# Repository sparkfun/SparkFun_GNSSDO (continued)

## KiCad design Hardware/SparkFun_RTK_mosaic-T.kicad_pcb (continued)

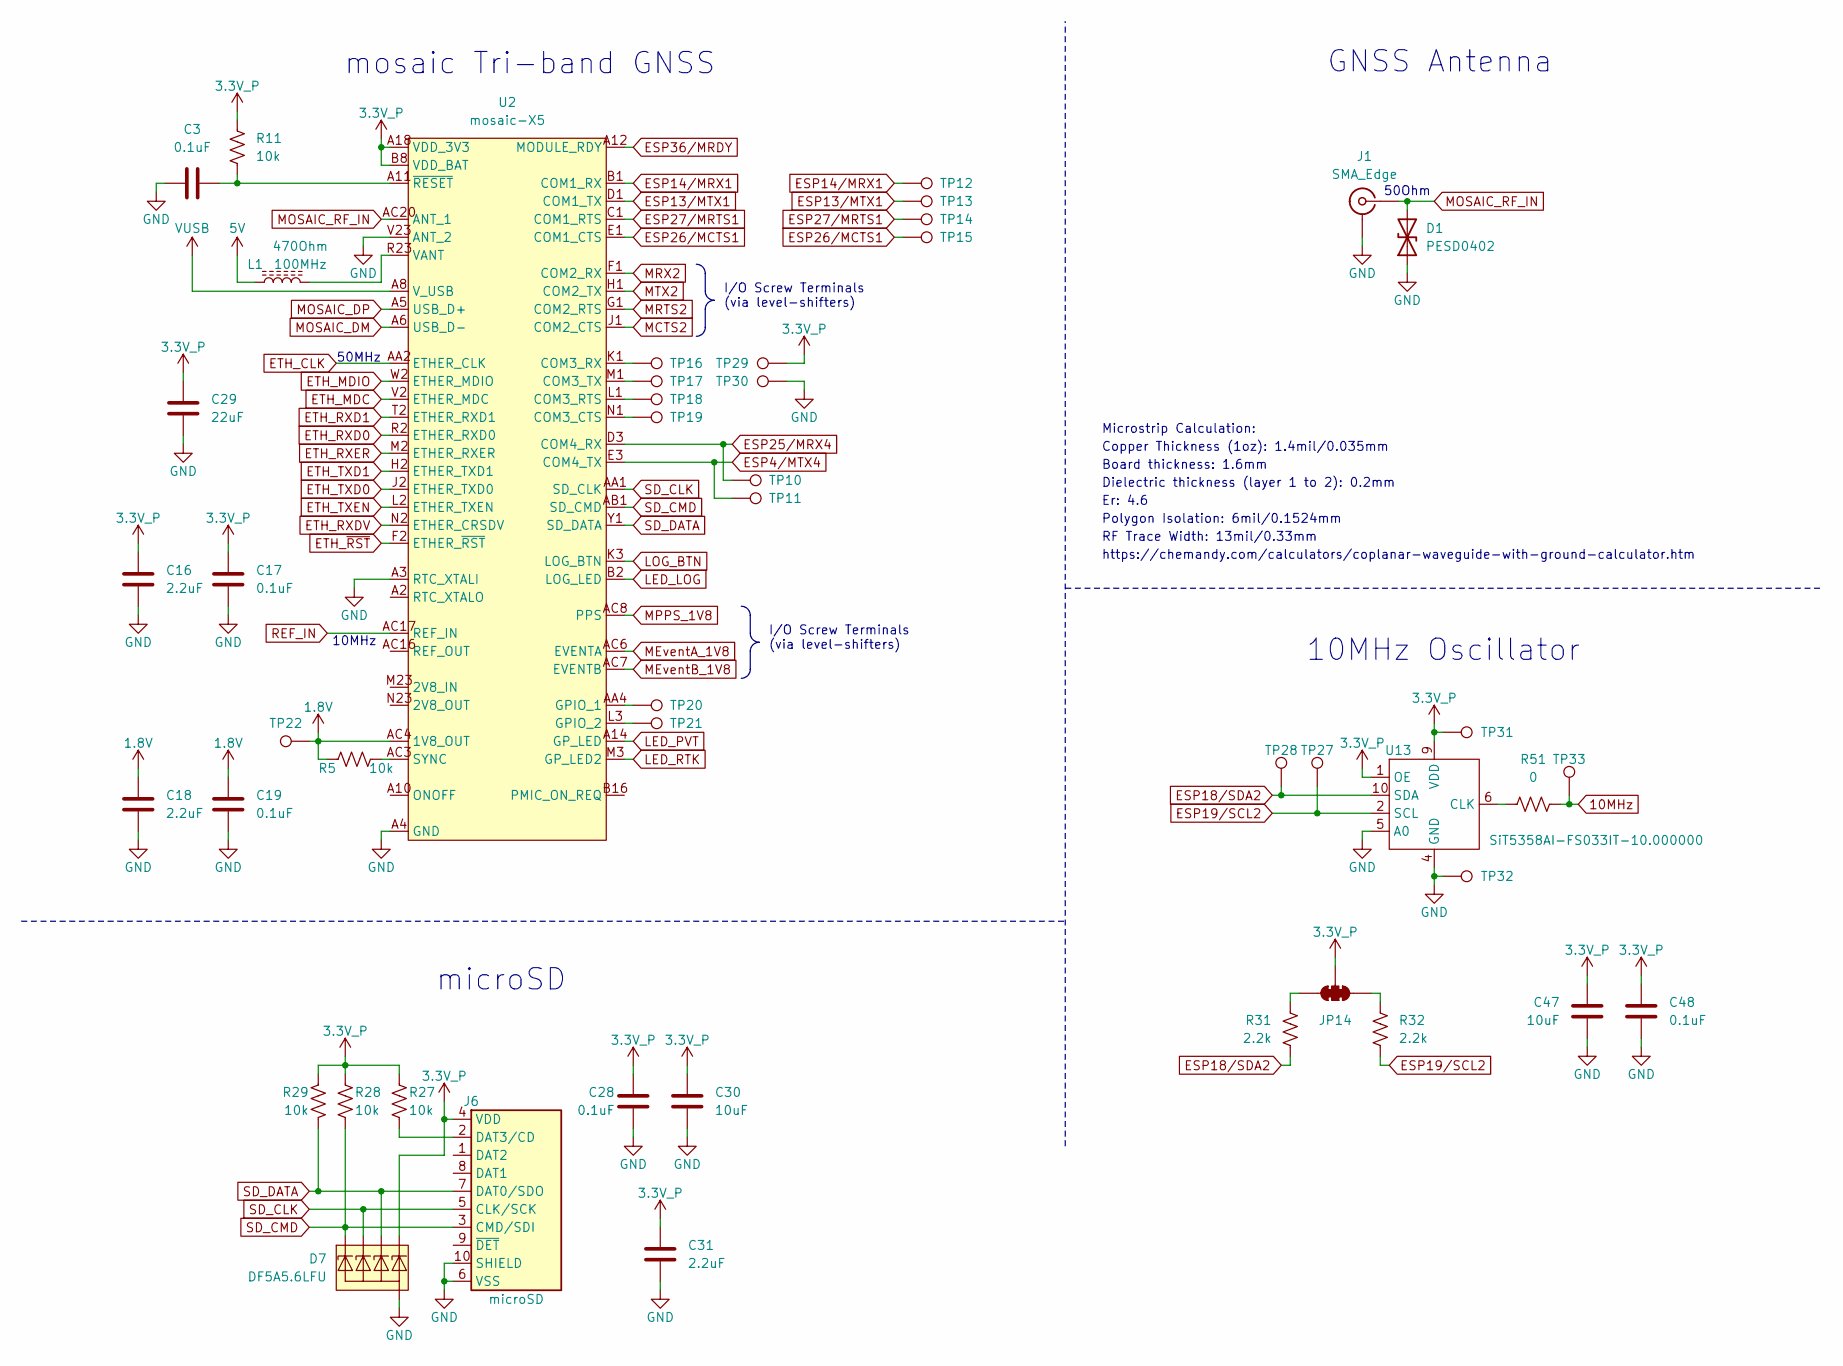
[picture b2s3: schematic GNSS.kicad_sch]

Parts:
C3, C17, C19, C28, C48: 0.1uF; C_0603_1608Metric; Voltage 25V; Tolerance 20%
C16, C18, C31: 2.2uF; C_0603_1608Metric; Voltage 10V; Tolerance 20%
C29: 22uF; C_0603_1608Metric; Voltage 6.3V; Tolerance 20%
C30, C47: 10uF; C_0603_1608Metric; Voltage 10V; Tolerance 20%
D1: PESD0402; C_0402_1005Metric
D7: DF5A5.6LFU; SOT-353
J1: SMA_Edge
J6: microSD; microSD_External_Pin
JP14: Jumper_3_NC-2_Trace
L1: 470Ohm; C_0603_1608Metric
R5, R11, R27, R28, R29: 10k; R_0603_1608Metric
R31, R32: 2.2k; R_0603_1608Metric
R51: 0; R_0603_1608Metric
TP10, TP11, TP12, TP13, TP14, TP15, TP16, TP17, TP18, TP19, TP20, TP21, TP22, TP27, TP28, TP29, TP30, TP31, TP32, TP33: PTH; 1x01
U2: mosaic-X5; MOSAIC_LGA
U13: SiT5358AI-FS033IT-10.000000; Ceramic_QFN_5.0x3.2mm-10

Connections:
1.8V: C18.1, C19.1, R5.2, TP22.1, U2.AC4 (1V8_OUT); also elsewhere on the board
3.3V_P: C16.1, C17.1, C28.1, C29.1, C30.1, C31.1, C47.1, C48.1, D7.5 (K4), J6.4 (VDD), JP14.2 (C), R11.2, R27.2, R28.2, R29.2, TP29.1, TP31.1, U2.A18 (VDD_3V3), U2.A19 (VDD_3V3), U2.A20 (VDD_3V3), U2.B8 (VDD_BAT), U2.B18 (VDD_3V3), U2.B19 (VDD_3V3), U2.B20 (VDD_3V3), U2.C18 (VDD_3V3), U2.C19 (VDD_3V3), U2.C20 (VDD_3V3), U13.1 (OE), U13.9 (VDD); also elsewhere on the board
5V: L1.1; also elsewhere on the board
10MHz: R51.1, TP33.1; also elsewhere on the board
ESP4/MTX4: TP11.1, U2.E3 (COM4_TX); also elsewhere on the board
ESP13/MTX1: TP13.1, U2.D1 (COM1_TX); also elsewhere on the board
ESP14/MRX1: TP12.1, U2.B1 (COM1_RX); also elsewhere on the board
ESP18/SDA2: R31.2, TP28.1, U13.10 (SDA); also elsewhere on the board
ESP19/SCL2: R32.2, TP27.1, U13.2 (SCL); also elsewhere on the board
ESP25/MRX4: TP10.1, U2.D3 (COM4_RX); also elsewhere on the board
ESP26/MCTS1: TP15.1, U2.E1 (COM1_CTS); also elsewhere on the board
ESP27/MRTS1: TP14.1, U2.C1 (COM1_RTS); also elsewhere on the board
ESP36/MRDY: U2.A12 (MODULE_RDY); also elsewhere on the board
ETH_CLK: U2.AA2 (ETHER_CLK); also elsewhere on the board
ETH_MDC: U2.V2 (ETHER_MDC); also elsewhere on the board
ETH_MDIO: U2.W2 (ETHER_MDIO); also elsewhere on the board
ETH_RXD0: U2.R2 (ETHER_RXD0); also elsewhere on the board
ETH_RXD1: U2.T2 (ETHER_RXD1); also elsewhere on the board
ETH_RXDV: U2.N2 (ETHER_CRSDV); also elsewhere on the board
ETH_RXER: U2.M2 (ETHER_RXER); also elsewhere on the board
ETH_TXD0: U2.J2 (ETHER_TXD0); also elsewhere on the board
ETH_TXD1: U2.H2 (ETHER_TXD1); also elsewhere on the board
ETH_TXEN: U2.L2 (ETHER_TXEN); also elsewhere on the board
ETH_~RST: U2.F2 (ETHER_~RST); also elsewhere on the board
GND: C3.1, C16.2, C17.2, C18.2, C19.2, C28.2, C29.2, C30.2, C31.2, C47.2, C48.2, D1.1 (A1), D7.2 (A), J1.2 (Ext), J6.6 (VSS), J6.10 (SHIELD), TP30.1, TP32.1, U2.A3 (RTC_XTALI), U2.A4 (GND), U2.A7 (GND), U2.A15 (GND), U2.A16 (GND), U2.A17 (GND), U2.A21 (GND), U2.A22 (GND), U2.A23 (GND), U2.AA13 (GND), U2.AA14 (GND), U2.AA15 (GND), U2.AA16 (GND), U2.AA17 (GND), U2.AA18 (GND), U2.AA19 (GND), U2.AA20 (GND), U2.AA21 (GND), U2.AA22 (GND), U2.AA23 (GND), U2.AB2 (GND), U2.AB3 (GND), U2.AB4 (GND), U2.AB5 (GND), U2.AB6 (GND), U2.AB7 (GND), U2.AB8 (GND), U2.AB13 (GND), U2.AB14 (GND), U2.AB15 (GND), U2.AB16 (GND), U2.AB17 (GND), U2.AB18 (GND), U2.AB19 (GND), U2.AB20 (GND), U2.AB21 (GND), U2.AB22 (GND), U2.AB23 (GND), U2.AC13 (GND), U2.AC15 (GND), U2.AC18 (GND), U2.AC19 (GND), U2.AC21 (GND), U2.AC22 (GND), U2.AC23 (GND), U2.B4 (GND), U2.B5 (GND), U2.B6 (GND), U2.B7 (GND), U2.B13 (GND), U2.B17 (GND), U2.B21 (GND), U2.C4 (GND), U2.C7 (GND), U2.C15 (GND), U2.C16 (GND), U2.C17 (GND), U2.C23 (GND), U2.D2 (GND), U2.D21 (GND), U2.D22 (GND), U2.D23 (GND), U2.E2 (GND), U2.E21 (GND), U2.E22 (GND), U2.E23 (GND), U2.F21 (GND), U2.F22 (GND), U2.F23 (GND), U2.G2 (GND), U2.G21 (GND), U2.G23 (GND), U2.H21 (GND), U2.H22 (GND), U2.H23 (GND), U2.J21 (GND), U2.J22 (GND), U2.J23 (GND), U2.K2 (GND), U2.K21 (GND), U2.K22 (GND), U2.K23 (GND), U2.L21 (GND), U2.L22 (GND), U2.L23 (GND), U2.M21 (GND), U2.M22 (GND), U2.N21 (GND), U2.N22 (GND), U2.P1 (GND), U2.P2 (GND), U2.P3 (GND), U2.P21 (GND), U2.P22 (GND), U2.R3 (GND), U2.R21 (GND), U2.R22 (GND), U2.T21 (GND), U2.T22 (GND), U2.T23 (GND), U2.U2 (GND), U2.U21 (GND), U2.U22 (GND), U2.U23 (GND), U2.V21 (GND), U2.V22 (GND), U2.V23 (ANT_2), U2.W21 (GND), U2.W22 (GND), U2.W23 (GND), U2.Y2 (GND), U2.Y21 (GND), U2.Y22 (GND), U2.Y23 (GND), U13.4 (GND), U13.5 (A0); also elsewhere on the board
LED_LOG: U2.B2 (LOG_LED); also elsewhere on the board
LED_PVT: U2.A14 (GP_LED); also elsewhere on the board
LED_RTK: U2.M3 (GP_LED2); also elsewhere on the board
LOG_BTN: U2.K3 (LOG_BTN); also elsewhere on the board
MCTS2: U2.J1 (COM2_CTS); also elsewhere on the board
MEventA_1V8: U2.AC6 (EVENTA); also elsewhere on the board
MEventB_1V8: U2.AC7 (EVENTB); also elsewhere on the board
MOSAIC_DM: U2.A6 (USB_D-); also elsewhere on the board
MOSAIC_DP: U2.A5 (USB_D+); also elsewhere on the board
MOSAIC_RF_IN: D1.2 (A2), J1.1 (In), U2.AC20 (ANT_1)
MPPS_1V8: U2.AC8 (PPS); also elsewhere on the board
MRTS2: U2.G1 (COM2_RTS); also elsewhere on the board
MRX2: U2.F1 (COM2_RX); also elsewhere on the board
MTX2: U2.H1 (COM2_TX); also elsewhere on the board
unnamed: J6.2 (DAT3/CD), R27.1
unnamed: JP14.1 (A), R32.1
unnamed: JP14.3 (B), R31.1
unnamed: TP19.1, U2.N1 (COM3_CTS)
unnamed: TP18.1, U2.L1 (COM3_RTS)
unnamed: TP16.1, U2.K1 (COM3_RX)
unnamed: TP17.1, U2.M1 (COM3_TX)
unnamed: TP20.1, U2.AA4 (GPIO_1)
unnamed: TP21.1, U2.L3 (GPIO_2)
unnamed: R5.1, U2.AC3 (SYNC)
unnamed: C3.2, R11.1, U2.A11 (~RESET)
unnamed: R51.2, U13.6 (CLK)
REF_IN: U2.AC17 (REF_IN); also elsewhere on the board
SD_CLK: D7.3 (K2), J6.5 (CLK/SCK), U2.AA1 (SD_CLK)
SD_CMD: D7.1 (K1), J6.3 (CMD/SDI), R28.1, U2.AB1 (SD_CMD)
SD_DATA: D7.4 (K3), J6.7 (DAT0/SDO), R29.1, U2.Y1 (SD_DATA)
VANT: L1.2, U2.P23 (VANT), U2.R23 (VANT)
VUSB: U2.A8 (V_USB); also elsewhere on the board

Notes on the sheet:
Er: 4.6
Polygon Isolation: 6mil/0.1524mm
10MHz
I/O Screw Terminals (via level-shifters)
10MHz Oscillator
Dielectric thickness (layer 1 to 2): 0.2mm
Board thickness: 1.6mm
mosaic Tri-band GNSS
Microstrip Calculation:
50Ohm
https://chemandy.com/calculators/coplanar-waveguide-with-ground-calculator.htm
Copper Thickness (1oz): 1.4mil/0.035mm
50MHz
GNSS Antenna
microSD
RF Trace Width: 13mil/0.33mm

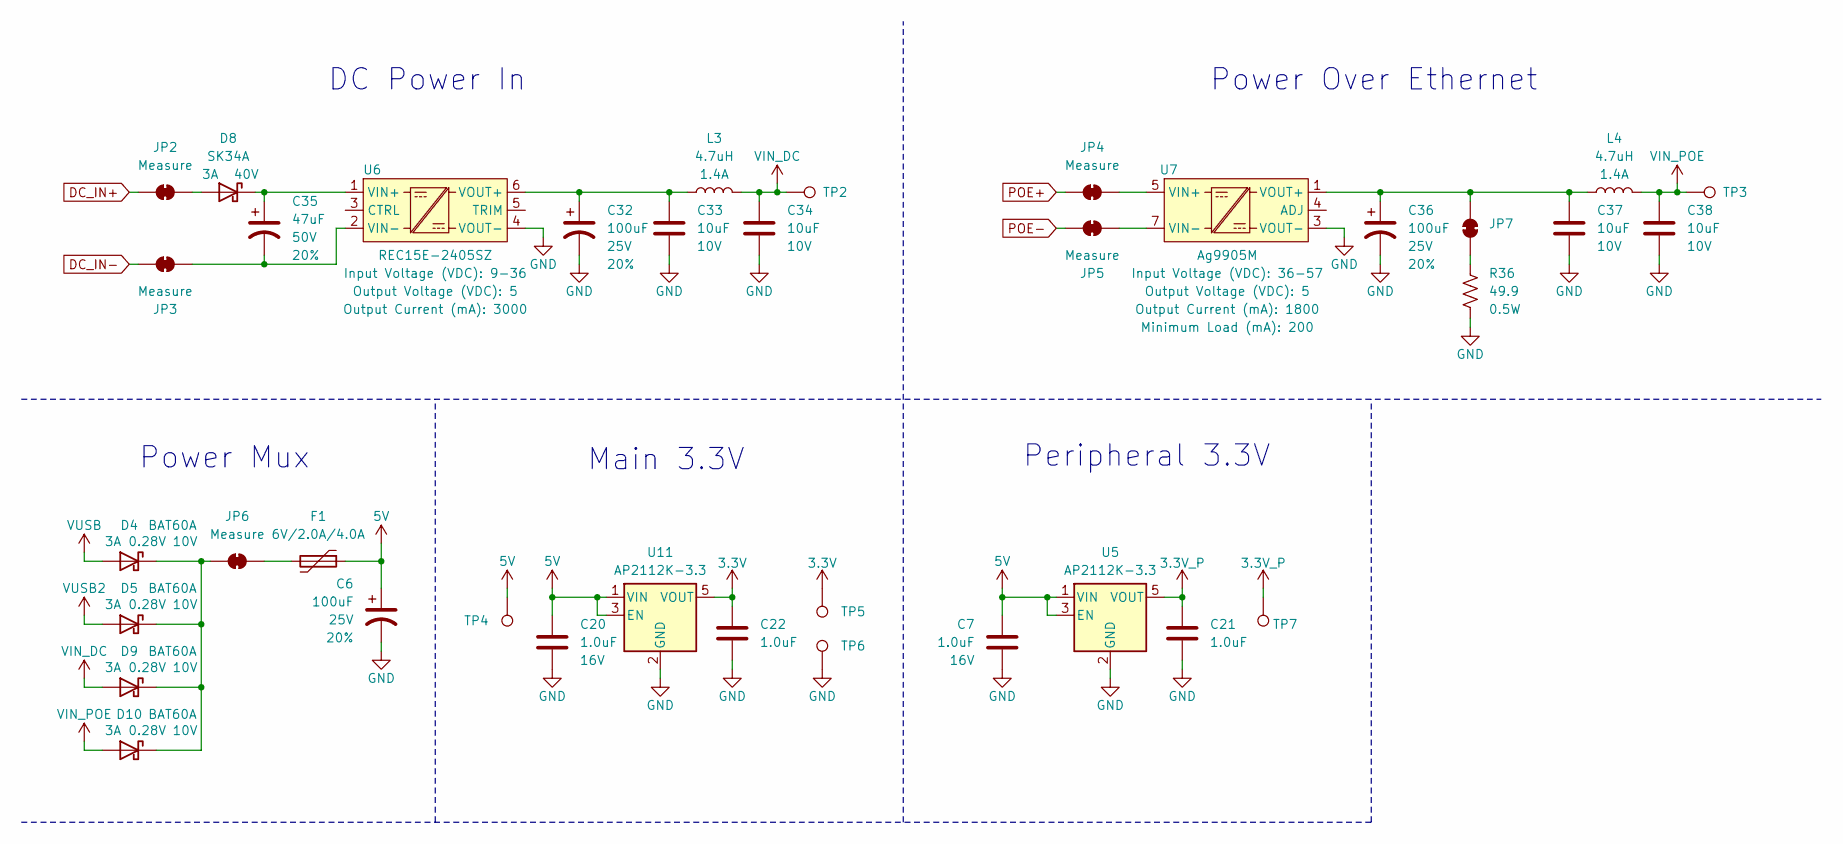
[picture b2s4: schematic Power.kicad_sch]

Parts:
C6, C32, C36: 100uF; PANASONIC_D; Voltage 25V; Tolerance 20%
C7, C20, C21, C22: 1.0uF; C_0603_1608Metric; Voltage 16V; Tolerance 10%
C33, C34, C37, C38: 10uF; C_0603_1608Metric; Voltage 10V; Tolerance 20%
C35: 47uF; PANASONIC_D; Voltage 50V; Tolerance 20%
D4, D5, D9, D10: BAT60A; SOD-323
D8: SK34A; SMA
F1: 6V/2.0A/4.0A; 1210
JP2, JP3, JP4, JP5, JP6: Measure; Jumper_2_PTH_SMD_Combo-NC
JP7: Jumper_2_NC_Trace
L3, L4: 4.7uH; 1008_2520Metric
R36: 49.9; R_1206_3216Metric; Tolerance 1%
TP2, TP3, TP4, TP5, TP6, TP7: PTH; 1x01
U5, U11: AP2112K-3.3; SOT23-5
U6: REC15E-2405SZ; REC15E; Input Voltage (VDC) 9-36; Output Voltage (VDC) 5
U7: Ag9905M; Ag9900M; Input Voltage (VDC) 36-57; Output Voltage (VDC) 5

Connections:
3.3V: C22.1, TP5.1, U11.5 (VOUT); also elsewhere on the board
3.3V_P: C21.1, TP7.1, U5.5 (VOUT); also elsewhere on the board
5V: C6.1, C7.1, C20.1, F1.1, TP4.1, U5.1 (VIN), U5.3 (EN), U11.1 (VIN), U11.3 (EN); also elsewhere on the board
DC_IN+: JP2.1 (A); also elsewhere on the board
DC_IN-: JP3.1 (A); also elsewhere on the board
GND: C6.2, C7.2, C20.2, C21.2, C22.2, C32.2, C33.2, C34.2, C36.2, C37.2, C38.2, R36.1, TP6.1, U5.2 (GND), U6.4 (VOUT-), U7.3 (VOUT-), U11.2 (GND); also elsewhere on the board
unnamed: D8.A, JP2.2 (B)
unnamed: C35.2, JP3.2 (B), U6.2 (VIN-)
unnamed: D4.C, D5.C, D9.C, D10.C, JP6.1 (A)
unnamed: F1.2, JP6.2 (B)
unnamed: JP7.1 (A), R36.2
unnamed: C36.1, C37.1, JP7.2 (B), L4.1, U7.1 (VOUT+), U7.2 (VOUT+)
unnamed: C35.1, D8.C, U6.1 (VIN+)
unnamed: C32.1, C33.1, L3.1, U6.6 (VOUT+)
POE+: JP4.1 (A); also elsewhere on the board
POE-: JP5.1 (A); also elsewhere on the board
VIN+: JP4.2 (B), U7.5 (VIN+), U7.6 (VIN+)
VIN-: JP5.2 (B), U7.7 (VIN-), U7.8 (VIN-)
VIN_DC: C34.1, D9.A, L3.2, TP2.1
VIN_POE: C38.1, D10.A, L4.2, TP3.1
VUSB: D4.A; also elsewhere on the board
VUSB2: D5.A; also elsewhere on the board

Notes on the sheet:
Power Over Ethernet
DC Power In
Peripheral 3.3V
Power Mux
Main 3.3V

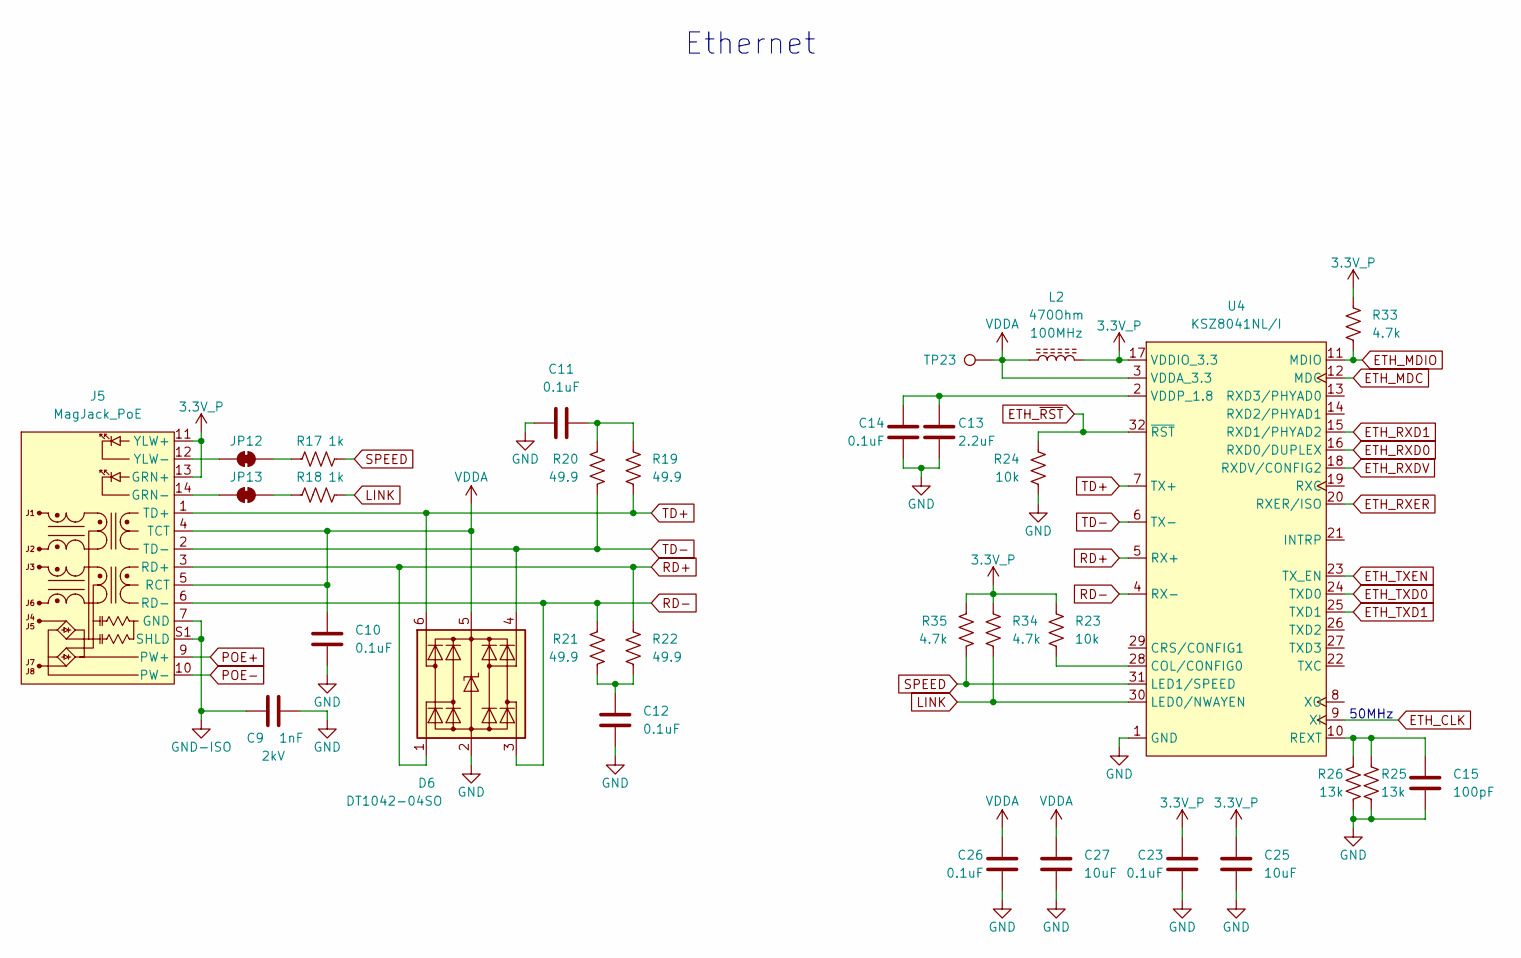
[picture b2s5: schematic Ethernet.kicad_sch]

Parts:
C9: 1nF; C_1206_3216Metric; Voltage 2kV; Tolerance 10%
C10, C11, C12, C14, C23, C26: 0.1uF; C_0603_1608Metric; Voltage 25V; Tolerance 20%
C13: 2.2uF; C_0603_1608Metric; Voltage 10V; Tolerance 20%
C15: 100pF; C_0603_1608Metric; Voltage 50V; Tolerance 10%
C25, C27: 10uF; C_0603_1608Metric; Voltage 10V; Tolerance 20%
D6: DT1042-04SO; SOT23-6
J5: MagJack_PoE; MagJack_PoE_RJ45
JP12, JP13: Jumper_2_NC_Trace
L2: 470Ohm; C_0603_1608Metric
R17, R18: 1k; R_0603_1608Metric
R19, R20, R21, R22: 49.9; R_0603_1608Metric; Tolerance 1%
R23, R24: 10k; R_0603_1608Metric
R25, R26: 13k; R_0603_1608Metric
R33, R34, R35: 4.7k; R_0603_1608Metric
TP23: PTH; 1x01
U4: KSZ8041NL/I; QFN-32

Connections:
3.3V_P: C23.1, C25.1, J5.11 (YLW+), J5.13 (GRN+), L2.2, R23.2, R33.1, R34.1, R35.1, U4.17 (VDDIO_3.3); also elsewhere on the board
ETH_CLK: U4.9 (XI); also elsewhere on the board
ETH_MDC: U4.12 (MDC); also elsewhere on the board
ETH_MDIO: R33.2, U4.11 (MDIO); also elsewhere on the board
ETH_RXD0: U4.16 (RXD0/DUPLEX); also elsewhere on the board
ETH_RXD1: U4.15 (RXD1/PHYAD2); also elsewhere on the board
ETH_RXDV: U4.18 (RXDV/CONFIG2); also elsewhere on the board
ETH_RXER: U4.20 (RXER/ISO); also elsewhere on the board
ETH_TXD0: U4.24 (TXD0); also elsewhere on the board
ETH_TXD1: U4.25 (TXD1); also elsewhere on the board
ETH_TXEN: U4.23 (TX_EN); also elsewhere on the board
ETH_~RST: R24.1, U4.32 (~RST); also elsewhere on the board
GND: C9.2, C10.2, C11.1, C12.2, C13.2, C14.2, C15.2, C23.2, C25.2, C26.2, C27.2, D6.2 (GND), R24.2, R25.2, R26.2, U4.1 (GND), U4.EP (GND); also elsewhere on the board
GND-ISO: C9.1, J5.7 (GND), J5.S1 (SHLD), J5.S2 (SHLD)
LINK: R18.1, R34.2, U4.30 (LED0/NWAYEN)
unnamed: C11.2, R19.1, R20.1
unnamed: C12.1, R21.2, R22.2
unnamed: J5.14 (GRN-), JP13.1 (A)
unnamed: J5.12 (YLW-), JP12.1 (A)
unnamed: JP12.2 (B), R17.2
unnamed: JP13.2 (B), R18.2
unnamed: R23.1, U4.28 (COL/CONFIG0)
unnamed: C15.1, R25.1, R26.1, U4.10 (REXT)
unnamed: C13.1, C14.1, U4.2 (VDDP_1.8)
POE+: J5.9 (PW+); also elsewhere on the board
POE-: J5.10 (PW-); also elsewhere on the board
RD+: D6.1 (I/O1), J5.3 (RD+), R22.1, U4.5 (RX+)
RD-: D6.3 (I/O2), J5.6 (RD-), R21.1, U4.4 (RX-)
SPEED: R17.1, R35.2, U4.31 (LED1/SPEED)
TD+: D6.6 (I/O4), J5.1 (TD+), R19.2, U4.7 (TX+)
TD-: D6.4 (I/O3), J5.2 (TD-), R20.2, U4.6 (TX-)
VDDA: C10.1, C26.1, C27.1, D6.5 (VCC), J5.4 (TCT), J5.5 (RCT), L2.1, TP23.1, U4.3 (VDDA_3.3)

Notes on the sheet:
50MHz
Ethernet

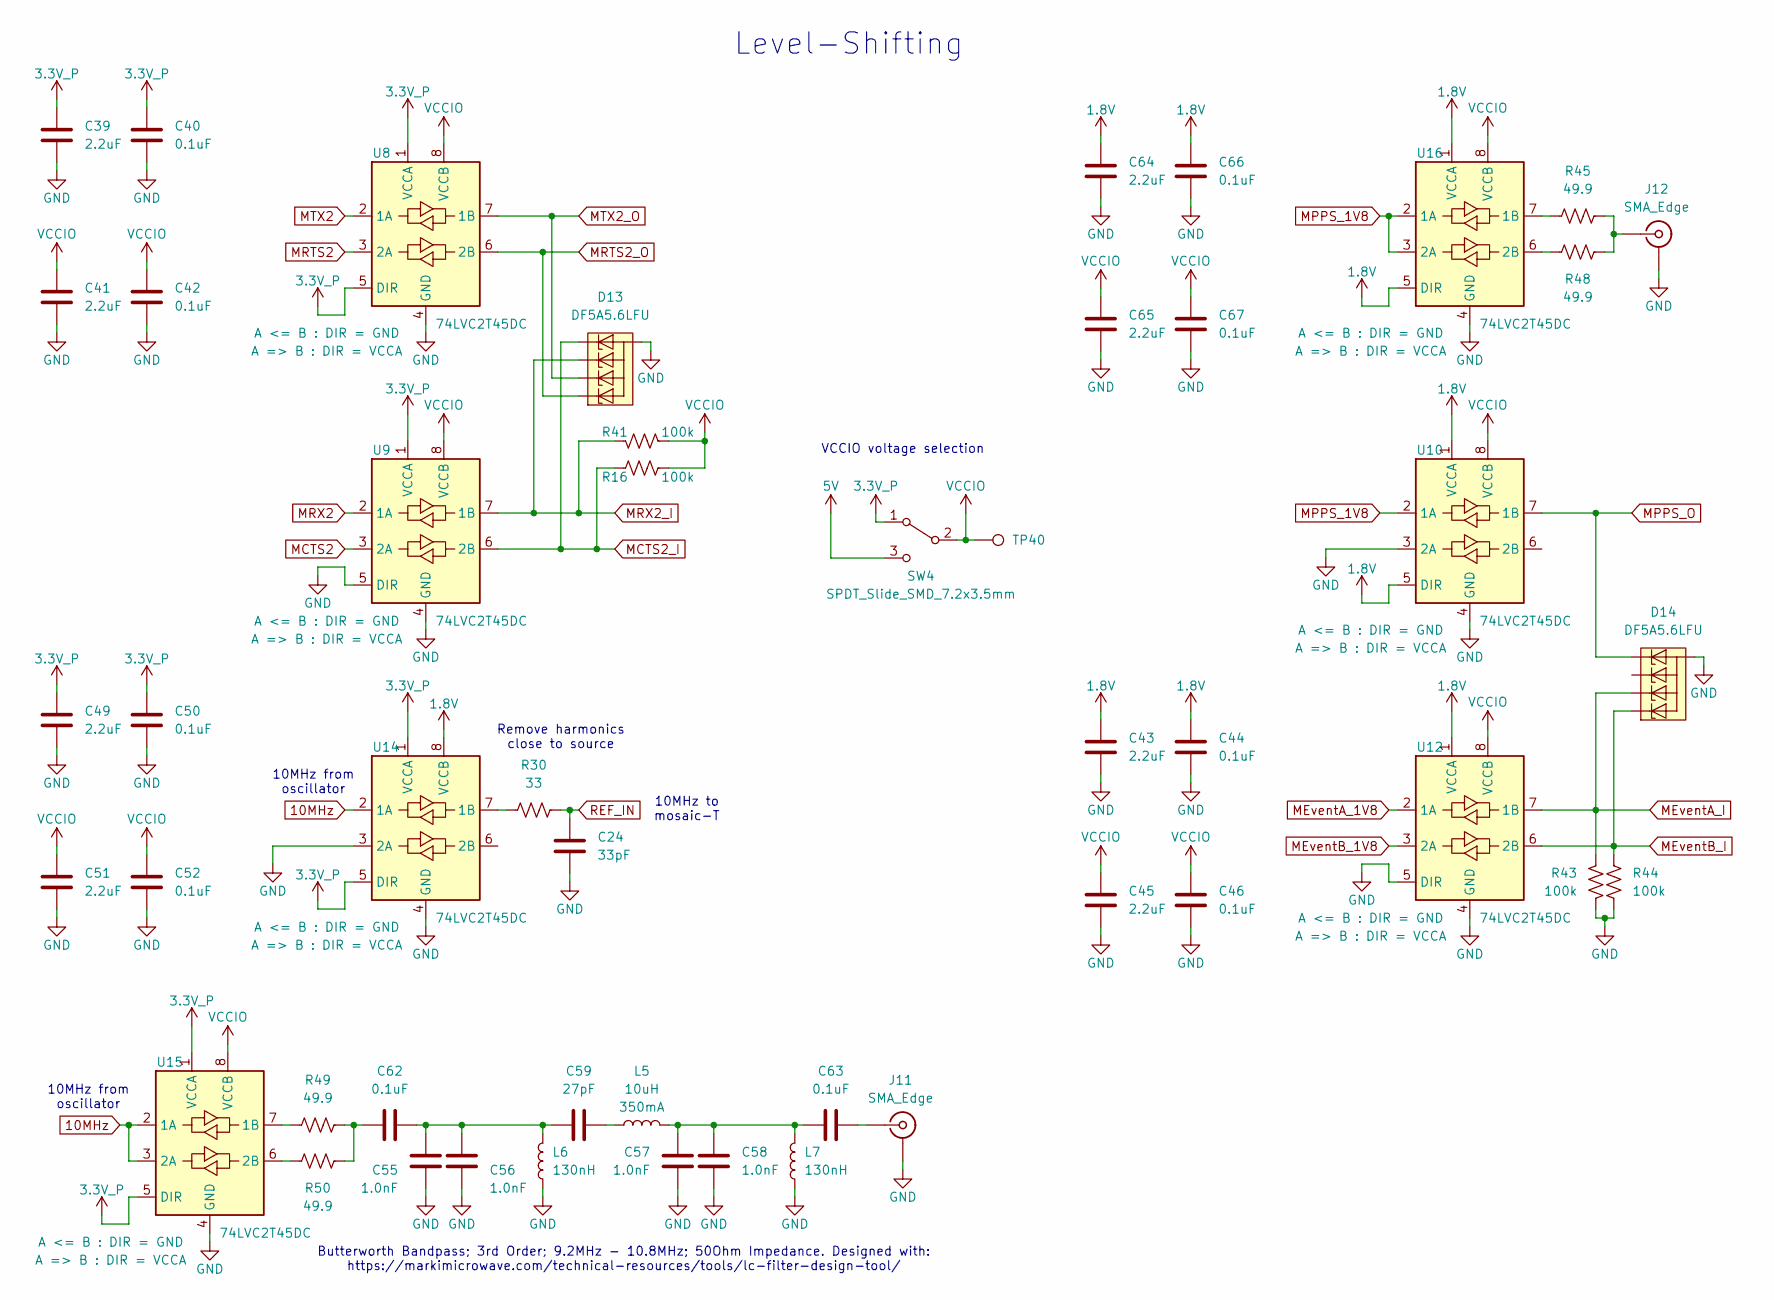
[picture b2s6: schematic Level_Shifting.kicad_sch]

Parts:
C24: 33pF; C_0603_1608Metric; Voltage 50V; Tolerance 5%
C39, C41, C43, C45, C49, C51, C64, C65: 2.2uF; C_0603_1608Metric; Voltage 10V; Tolerance 20%
C40, C42, C44, C46, C50, C52, C62, C63, C66, C67: 0.1uF; C_0603_1608Metric; Voltage 25V; Tolerance 20%
C55, C56, C57, C58: 1.0nF; C_0603_1608Metric; Voltage 50V; Tolerance 10%
C59: 27pF; C_0603_1608Metric; Voltage 50V; Tolerance 5%
D13, D14: DF5A5.6LFU; SOT-353
J11, J12: SMA_Edge
L5: 10uH; C_0805_2012Metric
L6, L7: 130nH; C_0603_1608Metric
R16, R41, R43, R44: 100k; R_0603_1608Metric
R30: 33; R_0603_1608Metric
R45, R48, R49, R50: 49.9; R_0603_1608Metric; Tolerance 1%
SW4: SPDT_Slide_SMD_7.2x3.5mm; Slide_DPDT_SMD_7.2x3.5mm; Mrg Part# AYZ0202
TP40: PTH; 1x01
U8, U9, U10, U12, U14, U15, U16: 74LVC2T45DC; VSSOP8_SOT765-1

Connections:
1.8V: C43.1, C44.1, C64.1, C66.1, U10.1 (VCCA), U10.5 (DIR), U12.1 (VCCA), U14.8 (VCCB), U16.1 (VCCA), U16.5 (DIR); also elsewhere on the board
3.3V_P: C39.1, C40.1, C49.1, C50.1, SW4.1 (A), U8.1 (VCCA), U8.5 (DIR), U9.1 (VCCA), U14.1 (VCCA), U14.5 (DIR), U15.1 (VCCA), U15.5 (DIR); also elsewhere on the board
5V: SW4.3 (C); also elsewhere on the board
10MHz: U14.2 (1A), U15.2 (1A), U15.3 (2A); also elsewhere on the board
GND: C24.2, C39.2, C40.2, C41.2, C42.2, C43.2, C44.2, C45.2, C46.2, C49.2, C50.2, C51.2, C52.2, C55.2, C56.2, C57.2, C58.2, C64.2, C65.2, C66.2, C67.2, D13.2 (A), D14.2 (A), J11.2 (Ext), J12.2 (Ext), L6.1, L7.1, R43.2, R44.2, U8.4 (GND), U9.4 (GND), U9.5 (DIR), U10.3 (2A), U10.4 (GND), U12.4 (GND), U12.5 (DIR), U14.3 (2A), U14.4 (GND), U15.4 (GND), U16.4 (GND); also elsewhere on the board
MCTS2: U9.3 (2A); also elsewhere on the board
MCTS2_I: D13.5 (K4), R16.2, U9.6 (2B); also elsewhere on the board
MEventA_1V8: U12.2 (1A); also elsewhere on the board
MEventA_I: D14.3 (K2), R43.1, U12.7 (1B); also elsewhere on the board
MEventB_1V8: U12.3 (2A); also elsewhere on the board
MEventB_I: D14.1 (K1), R44.1, U12.6 (2B); also elsewhere on the board
MPPS_1V8: U10.2 (1A), U16.2 (1A), U16.3 (2A); also elsewhere on the board
MPPS_O: D14.5 (K4), U10.7 (1B); also elsewhere on the board
MRTS2: U8.3 (2A); also elsewhere on the board
MRTS2_O: D13.1 (K1), U8.6 (2B); also elsewhere on the board
MRX2: U9.2 (1A); also elsewhere on the board
MRX2_I: D13.4 (K3), R41.2, U9.7 (1B); also elsewhere on the board
MTX2: U8.2 (1A); also elsewhere on the board
MTX2_O: D13.3 (K2), U8.7 (1B); also elsewhere on the board
unnamed: C55.1, C56.1, C59.1, C62.2, L6.2
unnamed: C57.1, C58.1, C63.1, L5.2, L7.2
unnamed: C59.2, L5.1
unnamed: C62.1, R49.1, R50.1
unnamed: C63.2, J11.1 (In)
unnamed: J12.1 (In), R45.1, R48.1
unnamed: R30.2, U14.7 (1B)
unnamed: R49.2, U15.7 (1B)
unnamed: R50.2, U15.6 (2B)
unnamed: R45.2, U16.7 (1B)
unnamed: R48.2, U16.6 (2B)
REF_IN: C24.1, R30.1; also elsewhere on the board
VCCIO: C41.1, C42.1, C45.1, C46.1, C51.1, C52.1, C65.1, C67.1, R16.1, R41.1, SW4.2 (B), TP40.1, U8.8 (VCCB), U9.8 (VCCB), U10.8 (VCCB), U12.8 (VCCB), U15.8 (VCCB), U16.8 (VCCB); also elsewhere on the board

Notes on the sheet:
10MHz from oscillator
Remove harmonics close to source
Level-Shifting
Butterworth Bandpass; 3rd Order; 9.2MHz - 10.8MHz; 50Ohm Impedance. Designed with: https://markimicrowave.com/technical-resources/tools/lc-filter-design-tool/
10MHz to mosaic-T
VCCIO voltage selection

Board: 4 copper layers, 339 parts (87 on the bottom side), 155 nets, no tracks yet.

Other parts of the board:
Ref**: Val**; OSHW_Logo_5mm
Ref**#2: Val**; SparkFun_RTK_15mm
kibuzzard-65A7F5A7: G***; kibuzzard-65A7F5A7
kibuzzard-65A7F5BC: G***; kibuzzard-65A7F5BC
kibuzzard-65A7F5CF: G***; kibuzzard-65A7F5CF
kibuzzard-65A7F5E3: G***; kibuzzard-65A7F5E3
kibuzzard-65A7F440, kibuzzard-65A7F440#2: G***; kibuzzard-65A7F440
kibuzzard-65A7F499: G***; kibuzzard-65A7F499
kibuzzard-65A7F511, kibuzzard-65A7F511#2: G***; kibuzzard-65A7F511
kibuzzard-65A7F548, kibuzzard-65A7F548#2: G***; kibuzzard-65A7F548
kibuzzard-65A7F771, kibuzzard-65A7F771#2: G***; kibuzzard-65A7F771
kibuzzard-65A7F891, kibuzzard-65A7F891#2: G***; kibuzzard-65A7F891
kibuzzard-66A11DB0: G***; kibuzzard-66A11DB0
kibuzzard-66A11DCF: G***; kibuzzard-66A11DCF
kibuzzard-66A11DE1: G***; kibuzzard-66A11DE1
kibuzzard-66A11DF6: G***; kibuzzard-66A11DF6
kibuzzard-66A11E3D: G***; kibuzzard-66A11E3D
kibuzzard-66A11E6E: G***; kibuzzard-66A11E6E
kibuzzard-66A11E07: G***; kibuzzard-66A11E07
kibuzzard-66A11E7B: G***; kibuzzard-66A11E7B
kibuzzard-66A11E14: G***; kibuzzard-66A11E14
kibuzzard-66A11E22: G***; kibuzzard-66A11E22
kibuzzard-66A11E31: G***; kibuzzard-66A11E31
kibuzzard-66A11E48: G***; kibuzzard-66A11E48
kibuzzard-66A11E61: G***; kibuzzard-66A11E61
kibuzzard-66A11E89: G***; kibuzzard-66A11E89
kibuzzard-66A11EB6: G***; kibuzzard-66A11EB6
kibuzzard-66A11ECA: G***; kibuzzard-66A11ECA
kibuzzard-66A11ED7: G***; kibuzzard-66A11ED7
kibuzzard-66A11EE6: G***; kibuzzard-66A11EE6
kibuzzard-66A11EF1: G***; kibuzzard-66A11EF1
kibuzzard-66A11F9C: G***; kibuzzard-66A11F9C
kibuzzard-66A11F21, kibuzzard-66A11F21#2: G***; kibuzzard-66A11F21
kibuzzard-66A11F39, kibuzzard-66A11F39#2: G***; kibuzzard-66A11F39
kibuzzard-66A11FB3: G***; kibuzzard-66A11FB3
kibuzzard-66A11FEE, kibuzzard-66A11FEE#2: G***; kibuzzard-66A11FEE
kibuzzard-66A120AA: G***; kibuzzard-66A120AA
kibuzzard-66A120EB: G***; kibuzzard-66A120EB
kibuzzard-66A121BE, kibuzzard-66A121BE#2: G***; kibuzzard-66A121BE
kibuzzard-66A121D2, kibuzzard-66A121D2#2: G***; kibuzzard-66A121D2
kibuzzard-66A122A4, kibuzzard-66A122A4#2: G***; kibuzzard-66A122A4
kibuzzard-66A122D2, kibuzzard-66A122D2#2: G***; kibuzzard-66A122D2
kibuzzard-66A211A5: G***; kibuzzard-66A211A5
kibuzzard-66A212C6: G***; kibuzzard-66A212C6
kibuzzard-66A212DB: G***; kibuzzard-66A212DB
kibuzzard-66A212E8: G***; kibuzzard-66A212E8
kibuzzard-66A212F8: G***; kibuzzard-66A212F8
kibuzzard-66A1201E: G***; kibuzzard-66A1201E
kibuzzard-66A1223B, kibuzzard-66A1223B#2: G***; kibuzzard-66A1223B
kibuzzard-66A2129F: G***; kibuzzard-66A2129F
kibuzzard-66A2131B: G***; kibuzzard-66A2131B
kibuzzard-66A12010: G***; kibuzzard-66A12010
kibuzzard-66A12027: G***; kibuzzard-66A12027
kibuzzard-66A12034: G***; kibuzzard-66A12034
kibuzzard-66A12099: G***; kibuzzard-66A12099
kibuzzard-66A12140: G***; kibuzzard-66A12140
kibuzzard-66A12152: G***; kibuzzard-66A12152
kibuzzard-66A12161: G***; kibuzzard-66A12161
kibuzzard-66A12184, kibuzzard-66A12184#2: G***; kibuzzard-66A12184
kibuzzard-66A12197, kibuzzard-66A12197#2: G***; kibuzzard-66A12197
kibuzzard-66A12248, kibuzzard-66A12248#2: G***; kibuzzard-66A12248
kibuzzard-66A12259, kibuzzard-66A12259#2: G***; kibuzzard-66A12259
kibuzzard-66A12273, kibuzzard-66A12273#2: G***; kibuzzard-66A12273
kibuzzard-66A12315, kibuzzard-66A12315#2: G***; kibuzzard-66A12315
kibuzzard-66A12334, kibuzzard-66A12334#2: G***; kibuzzard-66A12334
kibuzzard-66A12372, kibuzzard-66A12372#2: G***; kibuzzard-66A12372
kibuzzard-66A21191: G***; kibuzzard-66A21191
kibuzzard-66A21255: G***; kibuzzard-66A21255
kibuzzard-66A21305: G***; kibuzzard-66A21305
kibuzzard-66A21310: G***; kibuzzard-66A21310
kibuzzard-66A21341: G***; kibuzzard-66A21341
kibuzzard-66A21351: G***; kibuzzard-66A21351
kibuzzard-66A21378: G***; kibuzzard-66A21378
kibuzzard-65776CDC: G***; kibuzzard-65776CDC

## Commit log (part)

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2024-07-17 Change to DCTCXO
2024-07-21 More WIP
2024-07-23 Schematic complete
2024-07-23 PCB WIP
2024-07-23 Board edge components placed
2024-07-24 Ready for airwire review
2024-07-24 Add more silk
2024-07-25 Ready for routing
2024-07-25 Routing WIP
2024-07-26 Routed
2024-07-26 Panelized
2024-07-26 Add new PROD_IDs
2024-07-27 Updates to match latest KiCad library
2024-07-30 Docs updates
2024-07-30 Firmware very WIP
2024-07-31 Firmware WIP
2024-08-08 Add the consumer. Parse the SBF data for lat lon time IP etc.
2024-08-09 Firmware ~working
2024-08-12 Add build workflows
2024-08-12 Update workflows
2024-08-12 Push firmware Binary
2024-08-12 Update gitignore
2024-08-12 Add ESP Launchpad
2024-08-13 Remove ESP Launchpad - couldn't get it to work...
2024-08-14 Update 3D models on board
    Still missing the RP-SMA but otherwise good to go.
2024-08-15 Remove autosave files
2024-08-15 Update the 3D models.
2024-08-29 Fix SiT5358 symbol background
2024-09-18 Add PI control. Remove RTK_MOSAIC_X5
2024-09-19 Better GNSS debug
2024-09-19 Add CSV printConditions
2024-09-19 Correct NVM long settings
2024-09-19 Update default P and I terms
2024-09-19 Remove TCXO debug
2024-09-19 Default to 1s periodic print
2024-09-19 Remove UBX parser
2024-09-20 Add support for FugroTimeOffset
2024-09-23 Add the ability to prefer the non-composite GPS and Galileo clock biases
2024-09-23 Update comments
2024-09-24 Add soft and hard reset
2024-09-24 Better RTC sync and printConditions
2024-09-24 Fix FIRMWARE_VERSION
2024-09-24 Fix version prefix
2024-10-01 PCB symbol updates
2024-10-09 Add support for console-over-TCP
2024-10-10 Better TCP support - display the port on the OLED
2024-10-18 Updates for v1.0 PCB
2024-10-19 Update logo symbol and footprint
2024-10-21 Add jumpers for 2.8V and 1.8V In / Out
2024-10-21 GPSDO changes
2024-10-23 Add mounting holes for SiT5811 / Rakon oscillator
2024-10-24 Final changes before name change
2024-10-24 Change KiCad file name to SparkPNT_GPSDO
2024-10-24 Rename GPSDO_Firmware
2024-11-08 Final tweaks
2024-11-11 Update docs PCB images
2024-11-11 docs updates for GPSDO
2024-11-20 Rename to GNSSDO
2024-11-22 v1.2 - add support for SiT5811 and STP3593LF OCXOs
2024-11-25 Update the default P and I terms by TCXO type
2024-11-25 Better Bias display
2024-11-25 Add sticker artwork
2024-12-31 Update .gitignore. Add 1.2 binary
2024-12-31 Correct links. Remove references to "RTK"
2024-12-31 Better splash display
2025-01-06 Firmware v1.3 - enable Ethernet by default
2025-01-06 Add GNSSDO Plus hardware
2025-01-09 GNSSDO Plus: add 3-way splitter
2025-01-09 Firmware v1.4 - add soft reset to clear "Ready for SUF Download"
2025-01-09 GNSSDO+ WIP
2025-01-13 GNSSDO+ routed
2025-01-13 GNSSDO+ : update symbols and footprints
2025-01-14 GNSSDO Plus - ready for review
2025-01-15 Update AtomiChron docs
2025-01-15 Add clock bias performance
2025-01-20 GNSSDO+ PCB ready for protos
2025-02-06 v1.5
2025-02-06 Add ERROR print if no display is detected
2025-02-06 Store previousIP. Print previous and current IP in menuMain
    Print RX name, version and S/N in menuMain
    Print oscillatorType in menuMain
2025-02-19 Add product image
2025-02-25 Replace SparkFun w/ SparkPNT
    Replace instances of "SparkFun" with "SparkPNT"
    Add SparkPNT logo
2025-02-25 Update logo icons
    Adds new icons
    Replaces instances of old icons
2025-02-25 Add Katex Support
    Feature disabled
    - For future use
2025-02-25 Update favicon
2025-02-25 Move "generator" in footer
2025-02-25 Add cookie consent
    Add cookie consent to header
2025-02-25 Move files
    Move images into own folder/directory
2025-02-25 Update documentation build
    Update stylesheet
    Update build configuration
    - Add discourse icon
2025-02-25 Update ® icon
    Replace registered trademark icon for instances of AtomiChron
2025-02-25 Update logo icons
    Add Fugro logo
    Update use of "sfe-logo" to "sfe"
2025-02-25 Update build configuration
    Disable git-authors plug-in on CI
2025-02-25 Update links
    Update links for:
    - products
    - images
    Remove images for accessory box
2025-02-25 Switch bullet point style
    Switch from `*` to `-` in markdown
2025-02-25 Remove ASCII space
    Icon spacing in header fixed in mkdocs-material theme
2025-02-26 Update introduction.md
    - Move product feature info
    - Update "10MHz Signal" in comparison table
    - Update tutorials
    - Reorder list
    - Add tutorials
2025-02-26 Fix QR Codes
    Update stylesheet
    - Removed `iframe` element, to hide containers for videos when printing
    - Adjusted use classification for images in table
    - Fixes comparison table functionality
    - Removed misspelled file
    Update `troubleshooting_tips.md`
2025-02-26 Fix indentation and spacing
2025-02-27 Update resources.md
    Add articles and videos for timing and interference applications
2025-02-27 Replace faceplate images
    Update images with faceplate
    - Final product name
2025-02-27 Add/Remove Images
    Remove images no longer used
    Add images - for future use
2025-02-27 Update kit info
    Update information on items included in kit
    Rework how info is displayed
2025-02-27 Update header and links
    Clarify headers to USB drivers
2025-02-27 Update introduction.md
    Remove RTK Everywhere tutorial
2025-02-27 Update introduction.md
    Swap tutorial order in list
2025-02-27 Update troubleshooting_tips.md
    Remove vehicle power info
2025-02-27 Fix image link
2025-02-27 Update products
    Update product links
    Add more cables
    Add SMA adapters
2025-02-27 Update measurement info
    Add info to measuring dimensions
2025-02-27 Update admonitions
2025-02-27 Break up SMA info
    Use tabs and grids
2025-02-27 Update hardware_overview.md
    Move info into tabs
2025-02-27 Add spacing
    Provides a better separation of elements and sections
2025-02-27 Update YouTube Video
2025-02-27 Update quickstart images
2025-02-27 Update assembly images
2025-02-27 Rework information
    Rearrange how content is displayed
2025-02-27 Add 10MHz information
2025-02-27 Fix product links
2025-02-28 Correct POE.png
2025-02-28 Update RTK LED
2025-02-28 Add NMA definition
2025-02-28 Add Subscribing to Fugro AtomiChron
2025-02-28 Deployed 2f52194 with MkDocs version: 1.6.1
2025-02-28 docs tweaks
2025-02-28 Prep for v2.0
2025-02-28 Add support for GNSSDO+. Add support for no TCXO
2025-02-28 Extra time for eccf
2025-02-28 Update formatting
2025-02-28 Add datasheets
    Add datasheets for ESP32 and CH340
2025-02-28 Add icons
    Add logos for SiTime and Fugro
2025-02-28 Add resources
    Link additional datasheets
    Add resources for other manufacturers
    Add CSS to display Furgro logo
2025-02-28 Update privacy plugin
2025-02-28 Fix admonition
2025-02-28 Update Quick Start
2025-02-28 Update thumbnail image
2025-02-28 Replace workflow
    Update to latest build instructions
2025-02-28 Deployed 14f177d with MkDocs version: 1.6.1
2025-03-01 Deployed 3322a47 with MkDocs version: 1.6.1
2025-03-01 Correct ref to mosaic-T
2025-03-01 Deployed c3bede8 with MkDocs version: 1.6.1
2025-03-07 Add RX Clock Drift reporting
2025-04-15 Update 10MHz Reference
    Updated information and instructions for the 10MHz clock frequency reference switch
2025-04-15 Fix spacing
    Remove indentation
2025-04-16 Deployed 842437e with MkDocs version: 1.6.1
2025-06-06 GNSSDO+ v02 PCB - with DP5305 PoE module, PowerPath Controllers and MS8607 PHT sensor
2025-06-09 GNSSDO+ v02 PCB - panelized
2025-06-09 Deployed 1b878c9 with MkDocs version: 1.6.1
2025-06-14 Correct RTK references
2025-06-14 Deployed 73524dc with MkDocs version: 1.6.1
2025-08-14 Continue if display is not detected
2025-08-14 Add version 2.0 notes
2025-08-14 Deployed a19d8f7 with MkDocs version: 1.6.1
2025-09-10 Remove git-authors plugin
2025-09-10 Add custom SVG icons and update privacy plugin config
    Added new SVG icon files for hexagon and ublox logos in the overrides/.icons directory. Updated mkdocs.yml to conditionally enable the privacy plugin based on the CI environment variable.
2025-09-10 Deployed 878cc4f with MkDocs version: 1.6.1
2025-09-10 Update GitHub Actions badge
    Changed the GitHub Pages Deploy badge and link to reference the correct workflow file: build_documentation.yml instead of mkdocs.yml.
2025-09-10 Deployed 793b838 with MkDocs version: 1.6.1
2025-09-12 Update .gitignore
    Remove leftover merge conflict markers
    Consolidate duplicate entries
    Removes ignored file types
2025-09-12 Update footprints
    Fixes file path and position for the 3D models
2025-09-12 Update component documentation
    Updates the datasheet, manuals, etc. for the mosaic-T
2025-09-15 Deployed ab931c1 with MkDocs version: 1.6.1
2025-09-15 Deployed b56e82b with MkDocs version: 1.6.1
2025-09-15 Replace <center> and <sup> tags
    Update <center> tags to conform to HTML5 standards
    Replace <sup> tag with markdown notation
2025-09-15 Deployed 2965132 with MkDocs version: 1.6.1
2025-11-05 docs : add firmware upgrade
2025-11-05 Deployed c5aebe9 with MkDocs version: 1.6.1
2025-11-17 Add sysSource - see #11
2025-11-17 Fix for #10
2025-11-17 Add spm,Static,,auto - see #12
2025-11-17 Add Dockerfile and compile_with_dockerfile.bat
    This makes local compilation a whole lot easier - using the correct core and library versions
2025-11-17 Update docs - add compilation instructions
2025-11-19 Update version history
2025-11-27 Update Dockerfile
2025-11-27 Deployed 6756a08 with MkDocs version: 1.6.1
2026-02-03 v2.2 : add support for the MS8607 on GNSSDO+
2026-02-03 Update release notes
2026-02-03 Update docs
2026-02-04 Deployed 0dcd416 with MkDocs version: 1.6.1
2026-04-06 Many updates for GNSSDO+
2026-04-07 Improvements after retesting on GNSSDO
2026-04-07 v3.0
2026-04-09 Nearly there?
2026-04-11 After one successful lock-ins, one +ve, one -ve
2026-04-13 Rename rxStabilityForFrequencyLockError to rxStabilityForFrequencyLock
2026-04-13 Wrap the PID Derivative code in an ifdef
2026-04-13 Update comments / description
2026-04-13 Use actions/upload-artifact@v7
2026-04-13 Fix comment typo - add missing D
2026-04-14 Update GNSSDO KiCad files to match latest SparkFun library
2026-04-14 More docs updates
2026-04-15 Remove commented code
2026-04-15 Update default settings - these will be overwritten by beginTCXO
2026-04-15 Deployed 93a3624 with MkDocs version: 1.6.1
2026-04-15 Docs changes
2026-04-15 Deployed 2f57198 with MkDocs version: 1.6.1
2026-04-16 Deployed 70dfd20 with MkDocs version: 1.6.1
2026-04-17 Reduce PCB width by 1.5mm. Bump to v10
2026-04-17 Deployed 2e7493c with MkDocs version: 1.6.1
2026-04-24 Deployed e9d3be9 with MkDocs version: 1.6.1
2026-04-29 Update copyright year
2026-04-29 Update build workflow
2026-04-29 Deployed b905ab0 with MkDocs version: 1.6.1
2026-05-01 Update forum links
    Remove link to tech. assist page... 404; moved???
    Update links to community.sparkfun.com
2026-05-01 Deployed ec45cb4 with MkDocs version: 1.6.1
2026-05-06 Update product QR code
    Add QR code for GNSSDO+
    Update image link
2026-05-06 Update layout
    Video duplicated; moved below
    Changed grid card to be symmetric
2026-05-06 Change logo
    Renamed svg file (sparkpnt.svg -> sparkpnt-primary.svg)
    Added SparkPNT logo
    Utilize new logo
2026-05-06 Add announcement banner
    Deprecate hookup guide; link to new product manual
2026-05-06 Deployed 8b30a0b with MkDocs version: 1.6.1
2026-06-03 Deployed bc2cd74 with MkDocs version: 1.6.1
2026-06-24 Product rename
    Did not rename every instance of GNSSDO, GNSSDO+, GNSSDO(+)
    Updated README.md
    Updated product links
    Updated forum links
    Updated product manual redirect
2026-06-24 Deployed cdd4286 with MkDocs version: 1.6.1
2026-06-24 Fix video link
2026-06-24 Update button
2026-06-24 Deployed 9d65650 with MkDocs version: 1.6.1
2026-06-24 Replace video link
    Wrong URL
2026-06-24 Deployed 99276ef with MkDocs version: 1.6.1
